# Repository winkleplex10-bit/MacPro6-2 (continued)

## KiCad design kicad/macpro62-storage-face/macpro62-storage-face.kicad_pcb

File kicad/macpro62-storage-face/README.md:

# MP62 Face S storage module SM-1 rev A0: KiCad 9 project

4 × M.2 2280 NVMe behind an ASMedia ASM2824 PCIe Gen3 switch, on the MP62-FACE v0.1 outline. The plan, BOM, cost and RAID analysis are in `/workspace/macpro62-storage-board-plan.md`. The spec is `macpro62-face-module-spec-v0.1.md` §11.3 (update 3).

**Status: FLOORPLAN, not routed.**
- PCB: outline, holes, stackup (JLC06161H-2116, 6 layers), rule areas (both-side bus-bar keep-outs, core tab, J_PCIE plug zone), and every IC, connector, socket, standoff, inductor and bulk capacitor placed. Only the lug nets are on the PCB.
- `kicad-cli pcb drc`: **0 violations, 0 unconnected, 0 footprint errors**.
- Schematic (`macpro62-storage-face.kicad_sch`, one flat A0 sheet, label connectivity, 154 symbols): `kicad-cli sch erc`: **0 errors, 0 warnings**.

## Frame
- Same as the template. Module frame origin at the outline's bottom-left, viewed from the **core side**. Spec (X, Y) → KiCad (60 + X, 190 − Y).
- **F = core side** (ASM2824 on the die pad, switch support parts ≤ 2 mm).
- **B = outer side** (J_PCIE, J_AUX, 4 × M.2, power band).

## PLACEHOLDERS (replace before routing)
| Footprint | Why |
|---|---|
| `MP62_M2_MKey_SMT_H4.2_PLACEHOLDER` | Generic 67-pad M-key pattern (0.5 mm per row, rows offset 0.25), hold-downs and pegs are guesses. Use the LOTES APCI0107-P001A (LCSC C841661) drawing. The card-edge datum (origin) and the 2280 outline on F.Fab are correct per the M.2 form factor |
| `MP62_BGA-492_21x21mm_Layout25x25_P0.8mm_PLACEHOLDER` | ASM2824 ball map under NDA; 0.8 mm pitch assumed |
| `MP62_TI_RNN0018A_VQFN-HR-18_3.5x3.5mm_PLACEHOLDER` | TPS56C215 HotRod pads; use TI RNN0018A |
| `MP62_M2_Standoff_SMT_M2_Pad5.0` | Round pad; height must match the socket's card-bottom height (≈ 3.5 mm for H4.2, verify) |

Symbols with **logical** pin numbering: ASM2824, TPS259824, TPS56C215, TLV62585. Real pinouts: M.2 M-key, MCIO 124 (from the spec CSV), GH15, BL24C64A, TMP1075, 74LVC2G07, SPI NOR, LM74700.

## Layers
- User.1: core contact zones.
- User.2: outer height-zone lines.
- User.3: connector band.
- **User.4: M.2 card outlines** (host parts under a card ≤ 1.6 mm).
- Dwgs.User: stock X-bracket (**not fitted**, deviation D-S1 / spec C-19).
- Cmts.User: notes.

## Rebuild
```
python3 tools/make_footprints.py        # template footprints (MP62_Face.pretty)
python3 tools/make_storage_fps.py       # MP62_Storage.pretty
python3 tools/build_storage.py          # PCB floorplan (KiCad 9 pcbnew python)
python3 tools/postprocess.py            # stackup + netclasses (PCIE_85R, REFCLK_85R, PWR_12V, PWR_3V3)
python3 tools/build_sch.py              # MP62_Storage.kicad_sym + schematic
kicad-cli pcb drc --severity-all -o drc_report.txt macpro62-storage-face.kicad_pcb
kicad-cli sch erc --severity-all -o erc_report.txt macpro62-storage-face.kicad_sch
/workspace/cadenv/bin/python tools/floorplan.py   # floorplan_storage_SM1.png
```

## ICD rev 2 (2026-10-02)
- **U13 INA228** (VSSOP-10, FACE_SMB 0x40, ALERT → FACE_SMB_ALERT#) + **R520** 2 mΩ 2512 between +12V_PROT and +12V_PROT_S (ahead of U2) + C520; B side at (51.5, 143) / (44, 143) / (51.5, 140.5). DRC 0/0, ERC 0, 157 schematic instances. Renders not refreshed.

## ICD rev 3 / O-10 (2026-10-04 ≈ 09:10 ET, Aidan approved)
- **J1 (J_PCIE, MCIO 124 RA) X 43.5 → 47.0** (+3.5 mm), narrow-plug courtyard (±21.6). Zero-jog landing at BP fp6 s = +5.0. Nearest B courtyard MH080 0.34 mm; M.2 card bottom Y 28.5 vs J1 body top Y 24.57 (3.9 mm). `tools/floorplan.py` reads J_PCIE X from `face_geom.json`.
- Nothing routed besides the lug nets, so no re-route. DRC 0/0/0, ERC 0/0 (schematic unchanged). `floorplan_storage_SM1.png`, `render_core_side_F.png`, `render_outer_side_B.png` regenerated (kicad-cli svg + rsvg-convert).

## Next steps
1. Get the ASM2824 datasheet and ball map, plus the LOTES drawing.
2. Replace the placeholders.
3. Update the PCB from the schematic and place the ≈ 120 small passives.
4. Route: PCIe Gen3, ≤ 2 vias per lane; 3V3_SSD on the L4 plane plus B-side pours; 12 V pours.
5. Run DRC and get a JLC quote.

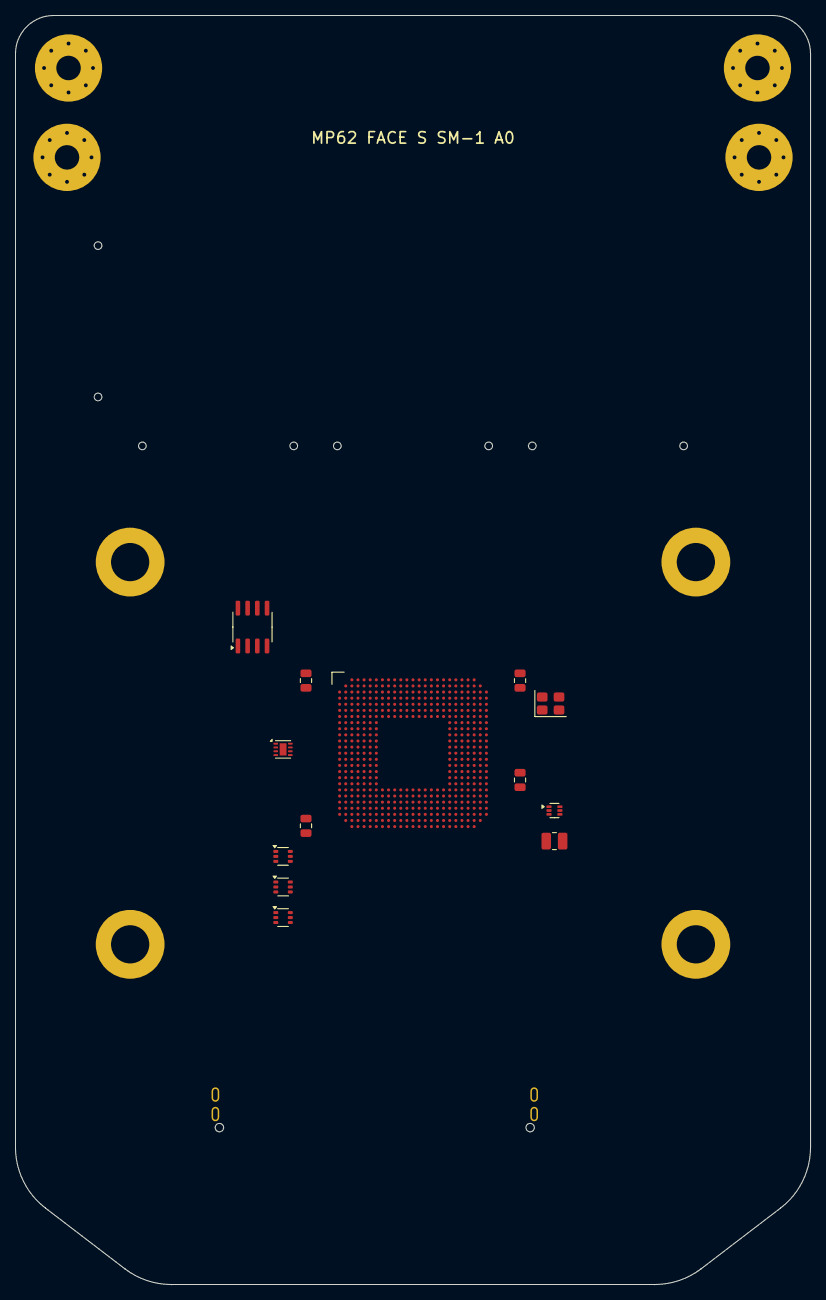
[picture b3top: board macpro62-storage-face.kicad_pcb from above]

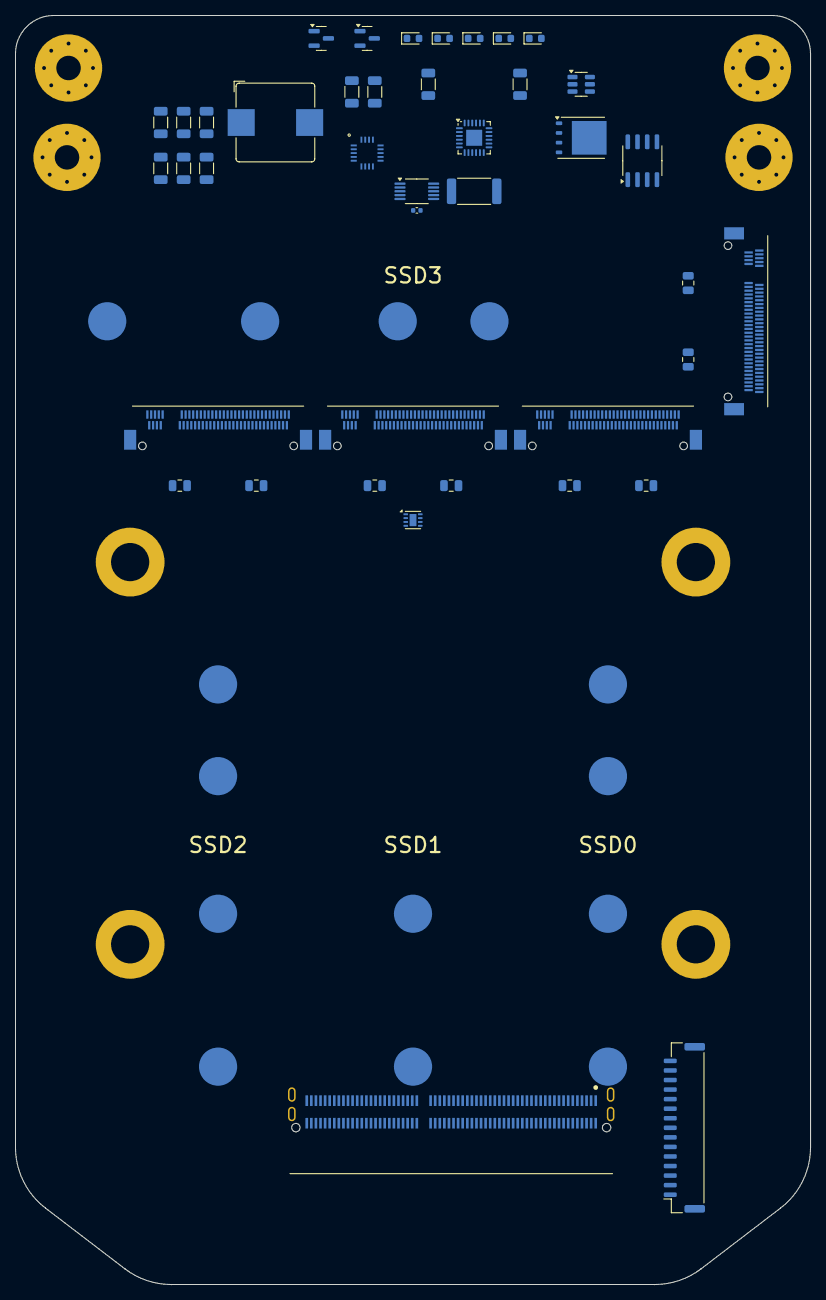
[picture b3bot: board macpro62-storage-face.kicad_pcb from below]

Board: 6 copper layers, 104.0 x 166.0 mm, 76 parts (55 on the bottom side), 2 nets.

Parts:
C10, C11: 10uF 25V; C_1206_3216Metric
C20, C21: 22uF 25V buck input; C_1206_3216Metric
C30, C31, C32, C33, C34, C35: 47uF 6.3V 3V3_SSD; C_1206_3216Metric
C40, C41, C42, C43, C44, C45, C46, C47: 22uF 0805 3V3 slot bulk (under card, <=1.6 mm); C_0805_2012Metric
C60, C61, C62, C63: 22uF switch bulk; C_0805_2012Metric
C520: 100nF U13 VS; C_0402_1005Metric
D1: SSD0 activity (DAS#); LED_0603_1608Metric
D2: SSD1 activity (DAS#); LED_0603_1608Metric
D3: SSD2 activity (DAS#); LED_0603_1608Metric
D4: SSD3 activity (DAS#); LED_0603_1608Metric
D5: 3V3_SSD power LED; LED_0603_1608Metric
D6, D7: BAT54A (DAS# -> MOD_LED# wired-OR); SOT-23
H1, H2, H3, H4: MOUNT D5.0 (screw + washer, NO bracket); MP62_FACE_MountHole_D5.0_Pad9.0
J1: J_PCIE MCIO124 RA G97R24332HR (lanes 0-7 used); MP62_MCIO_124P_RA_SFF-TA-1016
J3: J_AUX GH15 RA SM15B-GHS-TB (moved -6 mm Y); JST_GH_SM15B-GHS-TB_1x15-1MP_P1.25mm_Horizontal
J5: M.2 M-key H4.2 SSD0 (LOTES APCI0107-P001A); MP62_M2_MKey_SMT_H4.2_PLACEHOLDER
J6: M.2 M-key H4.2 SSD1 (LOTES APCI0107-P001A); MP62_M2_MKey_SMT_H4.2_PLACEHOLDER
J7: M.2 M-key H4.2 SSD2 (LOTES APCI0107-P001A); MP62_M2_MKey_SMT_H4.2_PLACEHOLDER
J8: M.2 M-key H4.2 SSD3 (LOTES APCI0107-P001A); MP62_M2_MKey_SMT_H4.2_PLACEHOLDER
J20: BUSBAR LUG site A +12V_IN (polarity TO MEASURE); MP62_FACE_BusBarLug_D3.2_Pad8.8
J21: BUSBAR LUG site A GND (polarity TO MEASURE); MP62_FACE_BusBarLug_D3.2_Pad8.8
J22: BUSBAR LUG site B +12V_IN (polarity TO MEASURE); MP62_FACE_BusBarLug_D3.2_Pad8.8
J23: BUSBAR LUG site B GND (polarity TO MEASURE); MP62_FACE_BusBarLug_D3.2_Pad8.8
L1: 1.0uH 10x10 >=15 A Isat; L_Bourns_SRP1038C_10.0x10.0mm
L2: 0.47uH 2520 (core buck); L_1008_2520Metric
MH030, MH230, MH330: M.2 standoff 2230; MP62_M2_Standoff_SMT_M2_Pad5.0
MH042, MH242, MH342: M.2 standoff 2242; MP62_M2_Standoff_SMT_M2_Pad5.0
MH060, MH160, MH260, MH360: M.2 standoff 2260; MP62_M2_Standoff_SMT_M2_Pad5.0
MH080, MH180, MH280, MH380: M.2 standoff 2280; MP62_M2_Standoff_SMT_M2_Pad5.0
Q1: N-MOSFET 30 V <=5 mOhm (reverse block); TDSON-8-1
R520: 2 mOhm 2512 shunt (+12V_PROT -> U2); R_2512_6332Metric
U1: ASM2824 PCIe Gen3 switch (JLC C9900092023); MP62_BGA-492_21x21mm_Layout25x25_P0.8mm_PLACEHOLDER
U2: TPS259824ONRGER eFuse I_LIM 5 A; Texas_RGE0024C_VQFN-24-1EP_4x4mm_P0.5mm_EP2.1x2.1mm
U3: LM74700-Q1 ideal-diode ctrl; SOT-23-6
U4: TPS56C215RNNR 3V3_SSD 12 A buck; MP62_TI_RNN0018A_VQFN-HR-18_3.5x3.5mm_PLACEHOLDER
U5: TLV62585 VDD_CORE buck (rail TBD per datasheet); SOT-563
U6: BL24C64A-SFRC ID EEPROM @0x50; SOIC-8_3.9x4.9mm_P1.27mm
U7: TMP1075DSGR @0x48; Texas_DSG0008A_WSON-8-1EP_2x2mm_P0.5mm_EP0.9x1.6mm
U8: SPI flash 25Q (switch config, TBD); SOIC-8_3.9x4.9mm_P1.27mm
U9: 74LVC2G07 PERST# fan-out SSD0/1; SOT-363_SC-70-6
U10: 74LVC2G07 PERST# fan-out SSD2/3; SOT-363_SC-70-6
U11: TMP1075DSGR @0x49 THERM_TRIP# (under SSD1, <=1.6 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; Texas_DSG0008A_WSON-8-1EP_2x2mm_P0.5mm_EP0.9x1.6mm
U12: 74LVC2G07 switch PERST# gate (PG_ALL); SOT-363_SC-70-6
U13: INA228 @0x40 FACE_SMB, ALERT -> FACE_SMB_ALERT#; VSSOP-10_3x3mm_P0.5mm
Y1: 25 MHz (populate only if ASM2824 needs it); Crystal_SMD_3225-4Pin_3.2x2.5mm

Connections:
+12V_IN: J20.1, J22.1
GND: J21.1, J23.1

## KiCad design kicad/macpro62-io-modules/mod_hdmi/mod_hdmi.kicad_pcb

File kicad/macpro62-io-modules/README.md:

> **Rev 2026-10-04 ≈ 10:40 ET (MOD-A + MOD-H hand-routed, real DF40 + HDMI land patterns; not pushed):**
> - **Real Hirose DF40 lands** (`../macpro62-io-board/tools/make_fps_modules.py`, Hirose DF40 catalogue + JLCEDA/EasyEDA Official Library (https://lceda.cn/ , https://easyeda.com) data in `tools/easyeda/`):
>   - module **DF40C-50DP-0.4V(51)** (Hirose 684-4014-0 51, LCSC **C424645**): 50 × 0.23 × 0.66 at 0.4, rows at ±1.355 (outer 3.37 / inner 2.05), plus 4 metal-fitting pads 0.35 × 0.66 at (±5.275, ±1.355), no net (Hirose: not for signal / power);
>   - main board **DF40C-50DS-0.4V(51)** (Hirose 684-4009-0 51, LCSC **C424646**): 50 × 0.20 copper 1.24 long at ±1.27, solderable 0.70 at ±1.54 (inner part under resist, per the Hirose land drawing), no fittings.
>   - Paddle 6.4 → **6.5** wide (8 lanes beyond the fitting-pad rows at |v| 1.685); flaps / flats re-derived in `modules_geom.py` (C +1.0, A +0.8, H +0.5 longer). PMI-50 pin numbering unchanged.
> - **MOD-H: real HOAUC HYC79-HDMIA19-105 (C711353)** (`tools/make_fp_hyc79.py`, EasyEDA checked against HOAUC drawing HYC-HDMI17102115): ONE row of 19 SMD pads 0.30 × 2.00 at 0.5, 2 dummy pads (no net), 3 THT GND legs Ø1.30 drill on **Ø1.90 pads = 0.30 ring** (placeholder shell ring was 0.20 < JLC 0.25).
> - **Hand fan-outs, no Freerouting on any module** (`tools/fanout_usba.py`, `tools/fanout_hdmi.py`; reports in `mod_*/fanout_report.json`, board totals in `mod_*/route_report.json`):
>   - MOD-A: SSRX / SSTX / D length-matched to **0.000** (were 2.70 / 2.64 / 2.52), 0 signal vias, 0.10 / 0.10 over the L2 hatch (90 Ω).
>   - MOD-H: staircase out of the pad row, bundle climbs over the outboard leg; DDC / HPD wrap down to row B; +5V drops to L2 at pin 18. **All four TMDS pairs intra-pair 0.000**, 0 signal vias, 0.08 / 0.15 (100 Ω) on solid L2.
>   - **New HDMI lane map** (`pmi50.ROLES["HDMI"]`, PMI-50 table itself unchanged): CK = USB2_A/B (k8/9 row A), D0 = LS_A1/A2 (k11/12), D1 = HS3 (k14/15), D2 = HS0 (k17/18), SCL / SDA / HPD = row B k8 / k9 / k11. Needed because the real single-row land fixes the planar order; the old map needed ~37 crossings. The main-board schematic follows automatically (JM11 re-wired, ERC 0).
> - **DRC:** mod_usbc / mod_usba / mod_hdmi 0 errors, 0 unconnected, 0 footprint errors (1 / 2 / 1 silk warnings). Panels 0 errors (7 / 8 silk). TDR coupons unchanged (0).
> - **finish fix:** the L1 GND island stitch vias now use the board's own GND net and keep clear of L2 non-GND copper (one had landed on the MOD-H +5V L2 run).
> - **Panels:** `panel_c50` 99.3 × 98.1 (was 97.2 × 97.8), `panel_a25` 74.0 × 82.2.

> **Rev 2026-10-04 ≈ 09:40 ET (MOD-C routed, 3-mil rule, fab outputs, panels):**
> - **MOD-C (`mod_usbc`) complete.**
>   - Real HOAUC HYCW417-USBC24-180B land pattern (`tools/make_fp_hycw417.py`). Source: JLCEDA/EasyEDA Official Library (https://lceda.cn/ , https://easyeda.com), checked against HOAUC drawing HYC-2212201742. The raw data is in `tools/easyeda/`.
>   - 24 SMD pads 0.27 × 1.30 at 0.50. **4 plated THT shell slots** 1.30 × 0.80 (pads grown to 1.80 × 1.30 for a 0.25 annular ring; pin-in-paste through the stiffener openings on User.1) and 2 NPTH Ø0.60 pegs.
>   - Hand fan-out (`tools/fanout_usbc.py`, no Freerouting). All four SS pairs leave on L1 with no vias. CC1/SBU2 take one L2 hop. VBUS uses a bar, an L2 port pour and wedge vias.
>   - DRC 0 errors / 0 unconnected (1 silk warning).
>   - SS intra-pair skew is 0.000 on all four pairs (chamfered bumps on the inner member near the pins). USB2 skew is 0.000 in orientation A and −2.09 mm in orientation B (B7 L2 hop).
> - **3-mil rule (JLC FPC +20 % when any width or gap is 2–3 mil):** every width and gap is now ≥ 0.078 (TMIN in `build_modules.py`).
>   - Paddle lanes went from 0.075 / 0.075 to 0.078 / 0.078. Netclass, DRC and diff-pair minimums are 0.078, zone minimum width is 0.078, and the Freerouting clearance is 0.082.
>   - MOD-A and MOD-H were re-routed. All three modules have DRC 0 errors and a minimum track of 0.078.
> - **USB-A PTH ring:** pads are now Ø1.25 (were Ø1.10 = 0.175 ring, below JLC's 0.18 absolute limit). The HDMI placeholder shell is still at 0.20.
> - **Skew (route_report.json):**
>   - MOD-A: D −2.65, SSRX +2.77, SSTX +2.64 mm. These are **not matched** (Freerouting fan-out around the THT pins). This is open and needs a MOD-C-style hand fan-out.
>   - MOD-H: CK −0.57, D0 −0.39, D1 −0.66, D2 −0.56 mm.
> - **TDR coupons:** a PADDLE_3MIL line (0.078 / 0.078) was added to `tdr_coupon_c50`. DRC 0.
> - **JLC fab outputs:** `python3 tools/make_fab.py` writes `<board>/fab/`:
>   - Gerber + Excellon zip (User.1 = FR4 stiffener layer),
>   - `*_bom_jlc.csv` (Comment, Designator, Footprint, LCSC Part #),
>   - `*_cpl_jlc.csv` (Designator, Mid X, Mid Y, Layer, Rotation).
>   - Covers the modules, coupons and panels. Check the JLC placement preview for rotation offsets.
> - **Panels:** `python3 tools/make_panel.py` → `panel/panel_c50` (6 × MOD-C + MOD-H + c50 coupon, 97.2 × 97.8) and `panel/panel_a25` (4 × MOD-A + a25 coupon, 74.0 × 82.2).
>   - Rails are 5 mm with copper, plus fiducials, tooling holes and 1.0 tabs on the stiffened edges. DRC 0 errors.
>   - MOD-A cannot share the C/H panel: it is a 25 µm-core (0.11) stack, and C/H are 50 µm (0.19).
> - **Rebuild:** `build_modules.py build|route|finish [mod]` → DRC → `build_tdr.py` → `make_fab.py` → `make_panel.py` → `make_fab.py` (again for the panels).

> **Rev 2026-10-02 ≈ 14:55 ET:**
> - **Geometry:** rebuilt on the new stack. The plate is 1.4 thick and glued, with the flex flat and no pocket, which moves everything 0.2. HDMI is back on the stock +X side: MOD-H is fitted rotated 180° into JM11 (rot 0).
> - **Routing status** (`python3 tools/build_modules.py build|route|finish [mod]`, then kicad-cli DRC; reports in `mod_*/drc_report.txt`, lengths in `mod_*/route_report.json`):
>   - **mod_usba:** complete. DRC 0 errors (2 silk warnings). Skew D −2.6, SSRX +2.7, SSTX +2.6, set by the THT pitch; compensate on the main board.
>   - **mod_hdmi:** complete. DRC 0 errors (1 silk warning). Skew CK −0.58, D0 −0.50, D1 −0.65, D2 −0.52.
>   - **mod_usbc:** **open.** 8 unconnected (A-row inner group CC1 / D± A / SBU1 / SSRX2±) and 1 clearance (CC2–shell tab 0.073). The placeholder shell tabs block the centre channel. Next step: the real HYCW417 land pattern plus a hand fan-out on L2 under the stiffened port.
> - **Router:** the DSN now offers a second via of 0.40 / 0.20 (JLC 2-layer FPC standard; extra cost only below a 0.15 hole) and allows max 500 passes.
> - **TDR coupons:** `tools/build_tdr.py` → `tdr/tdr_coupon_c50` (90 / 100 Ω solid and bend-hatch, 50 Ω SE) and `tdr/tdr_coupon_a25` (MOD-A 90 Ω cross-hatch). DRC 0.
> - **Pin 1:** `tools/check_pin1_3d.py` → `pin1_check.json`, `pin1_check_3d.png`. C1, C4, A1, A3 and HDMI all OK.
> - **Parts:**
>   - EEPROM BL24C02F-NTRC (C2828222).
>   - USB-A HC-USB3.0-L137-WJ (C7501870).
>   - ESD on the main board under each JMn: TPD4E02B04DQAR / TPD4E05U06DQAR, D200–D228.

# MP62 swappable port modules (D-IO16), rev A0 2026-10-02 ≈ 12:45 ET

Each USB-C, USB-A and HDMI port is a **flex-only module**. The receptacle is soldered straight to a JLC 2-layer FPC, like the stock audio jack on its flex. There is **no rigid PCB**. The FPC has a local FR4 1.0 stiffener under the port and a second one under the board-to-board header. The RJ45 jacks stay on the main board.

```
        plate (R 111.2) ── mouth normal to the plate (full plug seating)
            │ receptacle shell ── SUS304 0.2 sleeve (bonded) ── 1.0 collar ── under the clamp plate (MJF PA12 1.6, M2 → SMT standoffs on the main board)
            │ receptacle body (SMD pads / THT legs)
  ═══════════ FPC 0.11 ── PSA 0.05 ── FR4 stiffener 1.0 ── rests on the cradle ledges (MJF PA12, one cradle per group)
  ╰─ flap ─╮  180° C-fold, R 2.3–3.2
           ╰──── return run under the module ──── paddle: FR4 1.0 + DF40C-50DP (faces down) + 24C02 ID EEPROM + 100 nF
                                                   ▼ mates with DF40C-50DS (JM1–JM11) on the main board F side
```

## Modules

| Module | Slots | Receptacle (LCSC) | Mount | Stiffener (port) | Flat length | Flap / fold R | Sleeve seat → collar |
|---|---|---|---|---|---|---|---|
| MOD-C (`mod_usbc/`) | C1–C6 (one design; O-column modules are the same part rotated 180°) | HOAUC HYCW417-USBC24-180B (C5342202), vertical, 24 SMD signal pads + **4 plated THT shell legs 1.8** (2026-10-04, real land pattern), L 10.0. $1.13 at 1, $0.94 at 10. Only 196 in stock. | SMT + pin-in-paste shell legs (or selective solder) | 12.0 × 8.8 | 38.8 | 1.5 / 3.2 | 5.0 |
| MOD-A (`mod_usba/`) | A1–A4 | kinghelm KH-3.0AF180ZJ-11.5JB (C2979037), vertical USB 3.0, THT signal pins + shell legs, H 11.5, ≈ $0.16. **Only 2 in stock at 12:45 ET; 4 needed.** Second source: Hong Cheng HC-USB3.0-L137-WJ (C7501870, 645 in stock, ≈ $0.12), but it is H 13.7, which would drop the seat 2.2 mm and the fold R to about 1.2. Re-run modules_geom with CONN_H 13.7 before switching. | Selective solder through FPC + drilled FR4 | 16.8 × 8.8 | 39.7 | 0.5 / 2.3 | 6.65 |
| MOD-H (`mod_hdmi/`) | HDMI | HOAUC HYC79-HDMIA19-105 (C711353), vertical, SMD signals + THT shell legs, $0.49 at 1, 2,365 in stock | SMT + selective solder | 19.2 × 9.4 | 43.4 | 0.5 / 2.7 | 5.7 |

No all-SMD vertical USB-A 3.0 or HDMI receptacle is stocked at LCSC. Both use THT legs that pass through the FPC and the drilled FR4 stiffener. JLC FPC assembly offers THT (wave or selective solder, $23.57 per fixture). The leg tips sit inside the cradle's ledge window. Keep ≥ 0.5 mm below the tips.

## Force path (plug loads never pass through the flex or the solder joints)

| Load | Value (spec) | Path |
|---|---|---|
| Insertion (push) | USB-C ≤ 20 N, USB-A 3.0 ≤ 35 N, HDMI ≤ 44 N | Receptacle body bears on the FPC (compression only) → PSA → FR4 stiffener → cradle ledges (2 × 0.85 mm × stiffener length; HDMI 2 × 1.15). About 1 MPa on PA12. |
| Withdrawal (pull) | USB-C 8–20 N, USB-A ≥ 10 N, HDMI ≤ 39 N | Shell → bonded SUS304 sleeve → collar → clamp plate → 2 × M2 screws → blind SMT standoffs on the main board. The pads see no tension. Use **countersunk M2 (ISO 7046-1)** flush with the clamp-plate top; pan heads would hit the metal I/O frame (rev 2026-10-04 15:55 ET; HDMI post H25 now at (53.6, 114.35)). |
| Side / levering | Abuse | Sleeve in the clamp-plate aperture (0.1 clearance) + stiffener in the cradle pocket walls (0.1 clearance). |
| Main-board DF40 | 0 | The fold leaves slack. The DF40 carries only its own retention. |

Clamp plate deflection estimate (PA12, E 1.7 GPa, 1.6 thick, about 30 wide): 20 N at mid-span between the two C posts (21.5 mm) gives ≈ 0.24 mm, and ≈ 0.05 mm at the C1 overhang. That is acceptable, but add a rib or a third post if A0 parts flex.

Sleeve bond: solder if the shell is tin plated, structural epoxy (e.g. 3M DP420) if it is stainless. **TO MEASURE** (shell plating). The sleeve also grounds to the module's GND ring (coverlay opening) and carries a spring finger to the metal I/O frame.

## PMI-50 standard module interface (DF40C-50DP on the module ↔ DF40C-50DS on the main board)

Row A holds the odd pins (2k−1) and row B the even pins (2k).

| k | A | B | k | A | B |
|---|---|---|---|---|---|
| 1–6 | VBUS | VBUS | 18 | CC1 | HPD |
| 7–8 | GND | GND | 19 | CC2 | UTIL |
| 9 | HS0_P | HS2_P | 20 | GND | GND |
| 10 | HS0_N | HS2_N | 21 | ID_SCL | ID_SDA |
| 11 | GND | GND | 22 | 3V3_MOD | PRSNT# |
| 12 | HS1_P | HS3_P | 23 | LED# | GND |
| 13 | HS1_N | HS3_N | 24–25 | GND | GND |
| 14 | GND | GND | | | |
| 15 | USB2_DP | SBU1 | | | |
| 16 | USB2_DN | SBU2 | | | |
| 17 | GND | GND | | | |

- **Pin budget:** 12 VBUS pins (0.3 A each, 3.6 A total; USB-C 3 A is 83 % of rating), 17 GND, 21 signals.
- **PRSNT#:** tied to GND on the module. It drives U97 (TCA9555) inputs, and U97's INT# goes to PD_INT_N.
- **ID EEPROM:** a 24C02 at 0x50 on every module, behind U95/U96 (TCA9548A at 0x70/0x71). Channels: C1–C6 = U95 ch 0–5, A1–A2 = U95 ch 6–7, A3–A4 = U96 ch 0–1, HDMI = U96 ch 2.
- **USB-C mapping:** HS0 TX1, HS1 RX1, HS2 TX2, HS3 RX2.
- **USB-A mapping:** HS0 SSTX, HS1 SSRX. HS2/HS3, CC, SBU and HPD are not connected.
- **HDMI mapping (rev 2026-10-04, `pmi50.ROLES`):** row A: USB2_A/B = CK−/CK+, LS_A1/A2 = D0−/D0+, HS3_A/B = D1−/D1+, HS0_A/B = D2−/D2+; row B: LS_B1 = DDC SCL, LS_B2 = DDC SDA, SPARE_B1 = HPD; CEC / UTIL not connected; VBUS = +5V. (The table above is the old v1 layout; `pmi50.py` is the authority.)

## Flex construction (JLC FPC)

- **Layers:** 2-layer PI. MOD-A uses a 25 µm core (0.11 finished). MOD-C and MOD-H use a 50 µm core (0.19). L1 carries the signals (microstrip) and the VBUS strip. L2 is GND: solid on the tail, hatched in the bend, with VBUS bands under the port on MOD-C. Every copper width and gap is ≥ 0.078 (3 mil).
- **Impedance:** 90 Ω differential for USB and 100 Ω for TMDS. Set the widths with the JLC FPC impedance calculator. JLC does **not** measure impedance on FPC, so order a coupon and TDR it.
- **EMI silver film (optional):** User.2 over L1. It changes the trace widths. It needs ≥ 2 coverlay openings Ø ≥ 1.0 to GND about every 30 mm, must stay ≥ 0.8 from pads, and is removed under stiffeners.
- **Stiffeners:** FR4 1.0 on the B side, extending ≥ 1.0 beyond the pads, minimum width 3. Stainless 0.2 is the alternative if FR4 chips (JLC warns about this).
- **Bend zone:** User.4 plus a rule area (no vias or pads). Bend radius ≥ 2.3 mm, well above 10 × the thickness.
- **Layer use:** User.1 is the stiffener outline and User.3 the cradle ledge footprint.

## Swap procedure (system off)

1. Remove the 2 clamp-plate screws for the group and lift the plate.
2. Lift the module out of its cradle pocket.
3. Unplug the DF40 by lifting straight up at the paddle stiffener.
4. Reverse to fit. DF40 is rated for about 30 mating cycles, so log the swaps.

## Costs (per module, LCSC unit price, prototype quantity)

| Item | MOD-C | MOD-A | MOD-H |
|---|---|---|---|
| Receptacle | 1.13 | 0.16 | 0.49 |
| DF40C-50DP C424645 (module) + DF40C-50DS C424646 (main board), LCSC 2026-10-04 | 0.66 + 0.55 | same | same |
| 24C02 + 0201 cap | ≈ 0.2 | ≈ 0.2 | ≈ 0.2 |
| SUS304 sleeve (laser cut + bent) | 1–3 | 1–3 | 1–3 |
| FPC + 2 FR4 stiffeners | JLC FPC 5–10 pcs about $15–30 per design, plus a stencil | | |
| Assembly | SMT setup + $23.57 THT fixture (MOD-A, MOD-H) | | |

## Rebuild

```
python3 ../macpro62-io-board/tools/modules_geom.py        # modules.json (plate features → geometry + checks)
python3 ../macpro62-io-board/tools/make_fps_modules.py    # MP62_MOD.pretty + main-board cradle footprints
python3 tools/make_fp_hycw417.py                          # HOAUC HYCW417 land pattern from tools/easyeda/
python3 tools/make_fp_hyc79.py                            # HOAUC HYC79 HDMI land pattern from tools/easyeda/
python3 tools/build_modules.py build && python3 tools/build_modules.py finish   # all hand-routed (finish is not idempotent: always build first)
for m in mod_usbc mod_usba mod_hdmi; do kicad-cli pcb drc --severity-all -o $m/drc_report.txt $m/$m.kicad_pcb; done
python3 tools/build_tdr.py && python3 tools/make_fab.py && python3 tools/make_panel.py && python3 tools/make_fab.py
for m in mod_usbc mod_usba mod_hdmi; do python3 tools/plot_copper.py $m; done   # previews incl. *_fanout.png (pcbnew dump + cadenv matplotlib)
```

## Status

- **Outlines, stiffeners, bend zones, footprints:** placed. DRC 0 / 0 on all three (`*/drc_report.txt`).
- **Routing:** complete on all three, all hand-routed (2026-10-04 ≈ 10:40 ET), every pair intra-pair 0.000 except USB-C USB2 orientation B (−2.09, B7 hop).
- **Placeholders:** none on the modules any more (DF40C-50DP and HYC79 real since 2026-10-04 ≈ 10:40 ET). The USB-C pattern (HYCW417, EasyEDA, checked against the HOAUC drawing) is real. The USB-A pattern comes from the HC drawing and still needs checking against it.
- **EEPROM part:** the WLCSP-4 EEPROM (AT24CSW020-UUM0B class) has no LCSC number yet. If the paddle can grow by 1.5 mm, fall back to a SOT-23-5 24C02.
- **Geometry basis:** the geometry is for the default build (axis normal to the plate). Re-run `modules_geom.py` on the `_tilt12p5` features to get the stock-tilt variant.

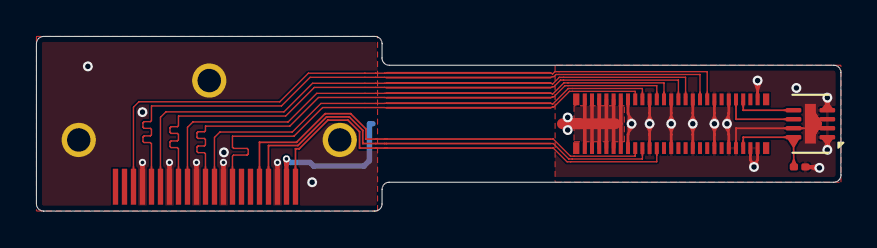
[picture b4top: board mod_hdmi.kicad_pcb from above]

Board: 2 copper layers, 44.7 x 9.7 mm, 4 parts (0 on the bottom side), 16 nets.

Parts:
C1: 100nF 0201 X5R 10V (3V3_MOD); C_0201_0603Metric
J1: MOD-H - HOAUC HYC79-HDMIA19-105 (C711353) 19 SMD 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; HOAUC_HYC79-HDMIA19-105
J2: DF40C-50DP-0.4V(51) C424645 -> JMn DF40C-50DS (PM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; MP62_Hirose_DF40C-50DP-0.4V
U1: BL24C02F-NTRC (C2828222) 24C02 ID EEPROM @0x50; DFN-8-1EP_2x3mm_P0.5mm_EP0.61x2.2mm

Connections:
3V3_MOD: C1.1, J2.46, U1.8
CK_N: J1.12, J2.15
CK_P: J1.10, J2.17
D0_N: J1.9, J2.21
D0_P: J1.7, J2.23
D1_N: J1.6, J2.27
D1_P: J1.4, J2.29
D2_N: J1.3, J2.33
D2_P: J1.1, J2.35
DDC_SCL: J1.15, J2.16
DDC_SDA: J1.16, J2.18
GND: C1.2, J1.2, J1.5, J1.8, J1.11, J1.17, J1.S, J2.13, J2.14, J2.19, J2.20, J2.25, J2.26, J2.31, J2.32, J2.37, J2.38, J2.41, J2.42, J2.44, J2.48, J2.49, J2.50, U1.1, U1.2, U1.3, U1.4, U1.7, U1.9
HPD: J1.19, J2.22
ID_SCL: J2.43, U1.6
ID_SDA: J2.45, U1.5
VBUS: J1.18, J2.1, J2.2, J2.3, J2.4, J2.5, J2.6, J2.7, J2.8, J2.9, J2.10, J2.11, J2.12

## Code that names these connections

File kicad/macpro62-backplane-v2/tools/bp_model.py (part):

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sym("M2_M_SATA", [(p, M2P.get(int(p), "NC%s" % p), L if int(p) % 2 else R) for p in m2pads] + [("MP", "MP", R)], "J",
    "MP62_BP:MP62_M2_MKey_SMT_H4.2_PLACEHOLDER", "M.2 Socket 3 M-key (SATA use only, host view: 47/49 = host TX, 41/43 = host RX)", w=20)
QFN80 = "Package_DFN_QFN:QFN-80-1EP_10x10mm_P0.4mm_EP3.4x3.4mm"
RP = {1: "GPIO4", 2: "GPIO5", 3: "GPIO6", 4: "GPIO7", 5: "IOVDD", 6: "GPIO8", 7: "GPIO9", 8: "GPIO10", 9: "GPIO11", 10: "DVDD", 11: "GPIO12",
      12: "GPIO13", 13: "GPIO14", 14: "GPIO15", 15: "IOVDD", 16: "GPIO16", 17: "GPIO17", 18: "GPIO18", 19: "GPIO19", 20: "GPIO20", 21: "GPIO21",
      22: "GPIO22", 23: "GPIO23", 24: "IOVDD", 25: "GPIO24", 26: "GPIO25", 27: "GPIO26", 28: "GPIO27", 29: "IOVDD", 30: "XIN", 31: "XOUT",
      32: "DVDD", 33: "SWCLK", 34: "SWDIO", 35: "RUN", 36: "GPIO28", 37: "GPIO29", 38: "GPIO30", 39: "GPIO31", 40: "GPIO32", 41: "IOVDD",
      42: "GPIO33", 43: "GPIO34", 44: "GPIO35", 45: "GPIO36", 46: "GPIO37", 47: "GPIO38", 48: "GPIO39", 49: "GPIO40_ADC0", 50: "IOVDD",
      51: "DVDD", 52: "GPIO41", 53: "GPIO42", 54: "GPIO43", 55: "GPIO44", 56: "GPIO45", 57: "GPIO46", 58: "GPIO47", 59: "ADC_AVDD",
      60: "IOVDD", 61: "VREG_AVDD", 62: "VREG_PGND", 63: "VREG_LX", 64: "VREG_VIN", 65: "VREG_FB", 66: "USB_DM", 67: "USB_DP",
      68: "USB_OTP_VDD", 69: "QSPI_IOVDD", 70: "QSPI_SD3", 71: "QSPI_SCLK", 72: "QSPI_SD0", 73: "QSPI_SD2", 74: "QSPI_SD1", 75: "QSPI_SS",
      76: "IOVDD", 77: "GPIO0", 78: "GPIO1", 79: "GPIO2", 80: "GPIO3", 81: "GND_EP"}
sym("RP2350B", [(str(k), v, L if k <= 40 or k == 81 else R) for k, v in RP.items()], "U", QFN80,
    "Raspberry Pi RP2350B QFN-80 (LCSC C42415655), pinout from the RP2350 datasheet", w=22)
sym("W25Q_SOIC8", [("1", "CS#", L), ("2", "DO(IO1)", L), ("3", "WP#(IO2)", L), ("4", "GND", L), ("8", "VCC", R), ("7", "HOLD#(IO3)", R), ("6", "CLK", R), ("5", "DI(IO0)", R)],
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def j1net(pin):
    s = j1sig[pin]
    if s in ("GND",): return "GND"
    if s.startswith("RSVD") or s in ("SMB_CLK", "SMB_DAT", "SMB_ALERT#", "GPIO0", "GPIO1", "GPIO2", "GPIO3", "BIOS_SEL", "RSTBTN#", "WAKE0#"):
        return None
    for pre, nm in (("FP_PET", "FP_TX"), ("FP_PER", "FP_RX"), ("FS_PET", "FS_TX"), ("FS_PER", "FS_RX")):
        if s.startswith(pre): return nm + s[len(pre):]           # FP_TX15_P ...
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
